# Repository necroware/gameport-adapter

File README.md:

# Necroware's GamePort Adapter

Many people from the retro community still have their beloved joysticks and
gamepads from the early days. These devices often live their lives somewhere in
the dark corners of our basements and we don't dare to throw them away, because
of nostalgic reasons. They remind us so much of our childhoods, where we played
our Wing Commanders, X-Wings, Descents and many other games. These old joysticks
were all made to be connected to the game port, usually on a sound card. But
by the end of 90's and beginning of 2000's game ports vanished from our
computers and were replaced by USB and our old joysticks disappeared into the
past. Today not everybody has a full retro PC and many people are using their
modern computer with  DOSBox to play the old games, sometimes with a modern
USB joystick. But wouldn't it be great to play the old games with the same
joystick which we used back then? And this is where this adapter comes into
play. It can be used to connect gameport joysticks to a USB port.

GamePort Adapter Videos:
* [Part 1: Introduction](https://youtu.be/tSJLgCD8jeM)
* [Part 2: Updates](https://youtu.be/947DewHwbsE)

## How does it work?

The adapter is built around Arduino Pro Micro, which uses the same ATmega32U4
microcontroller as Leonardo. This microcontroller has built-in USB HID
capabilities and can be used to build HID input devices, like joysticks. The
adapter itself is super simple, the main brainwork was invested into the
software. Very much simplified, it reads the joystick states and sends the data,
via USB, to the computer, which thinks that it is communicating with a USB 
joystick.

## What is special about this one?

There are already plenty of gameport to USB adapters for basic analog joysticks
and, as far as I know, there were some efforts to communicate with Sidewinder
joysticks by Microsoft as well. But there is no universal adapter, which would
work with different types of joysticks. This adapter implements multiple drivers
for various analog and digital joysticks, with an option to add more, in the 
future.

Features overview:
* Support for generic analog joysticks with 2/4 buttons and 2/4 axes
* Four switches to select joystick type
* Autodetection for various digital protocol joysticks
* Auto-Calibration
* Very low input lag

## What is the difference between analog and digital joystick?

Many people call button-only joysticks or gamepads digital. This is kind of
right, because a button is either pressed or not. You can't have an analog
values in between. However by digital, in this case, we mean something different.
A gameport contains 15 pins, 8 of which are used for joystick communication. 4
pins are for buttons and carry digital values in sense of on/off and 4 pins are
for analog axes, which deliver voltage somewhere between 0V and 5V. Joysticks
which were made in the early days used this pinout. They could have a
maximum of 4 buttons and 4 axes and were DOS compatible. Later, in the time of
Windows 95/98 many joysticks were made to be plugged into a gameport as well,
but they were not limited to 4 buttons and 4 axes. They had a lot more exciting
features, like hat switches and throttle controls. But how did this work? Well
the manufacturers implemented their drivers to communicate with the joystick via
gameport using a proprietary communication protocol. For example, by using one
pin of the gameport as clock and another one as data, the possibilities were
almost limitless. Such joysticks are called digital as well, because they used
digital protocols to communicate with the PC. And suddenly, many features were
possible, but the price of these features was the lost compatibility to DOS. You
couldn't just plug such a joystick into the gameport and expect it to work in
old DOS games. The plug was the same, but the signaling was completely different.

## Which joysticks does this adapter support?

Currently, the following drivers are implemented. To select the right driver, you
have to use four switches, as shown in the table. The switches may be changed or
extended in the future, so please pay attention to the updates.

Joystick Model               | Buttons | Axes  |  Hat | SW1-4 | Protocol   | Comments
-----------------------------|---------|-------|------|-------|------------|------------------------------------
Generic Analog               | 2       | 2     | 0    | 0000  | Analogue   |
Generic Analog               | 4       | 2     | 0    | 1000  | Analogue   |
Generic Analog               | 4       | 3     | 0    | 0100  | Analogue   | 3rd Axis is throttle
Generic Analog               | 4       | 4     | 0    | 1100  | Analogue   |
CH FlightStick               | 4       | 4     | 1    | 0010  | Analogue   |
CH F16 Combat Stick          | 10      | 3     | 1    | 0110  | Analogue   |
ThrustMaster                 | 4       | 3     | 1    | 1010  | Analogue   | FCS MARK I/II & PFCS
ThrustMaster Millenium 3D    | 6       | 4     | 1    | 0101  | TMDC       | 
Sidewinder GamePad           | 10      | 2     | 0    | 1110  | Sidewinder |
Sidewinder 3D Pro            | 8       | 4     | 1    | 1110  | Sidewinder |
Sidewinder 3D Pro Plus       | 9       | 4     | 1    | 1110  | Sidewinder | First version of Precision Pro
Sidewinder Precision Pro     | 16      | 4     | 1    | 1110  | Sidewinder | Shift doubbles the buttons
Sidewinder FFB Pro           | 16      | 4     | 1    | 1110  | Sidewinder | FFB not yet implemented
Sidewinder FFB Wheel         | 8       | 3     | 0    | 1110  | Sidewinder | FFB not yet implemented
Sidewinder Freestyle Pro     | 10      | 3     | 1    | 1110  | Sidewinder | 3rd axis is throttle
Gravis GamePad Pro           | 10      | 2     | 0    | 0001  | GrIP       |
Logitech WingMan Extreme     | 6       | 3     | 1    | 1001  | ADI        |
Logitech CyberMan 2          | 8       | 6     | 0    | 1001  | ADI        |
Logitech WingMan Interceptor | 9       | 3     | 3    | 1001  | ADI        | 2 hats are mapped as 4 axes
Logitech ThunderPad Digital  | 8       | 2     | 0    | 1001  | ADI        | Directional buttons mapped as 2 axes
Logitech WingMan Gamepad     | 11      | 2     | 0    | 1001  | ADI        | Directional buttons mapped as 2 axes
Logitech WingMan Light       | 2       | 2     | 0    | 0000  | Analogue   |

*Remarks:*

- Please pay attention to how the same switches are used for different families
of digital devices. This is possible due to fully digital communication. Using
this method, the adapter implements autodetection as soon as it knows, that it
is connected to a digital joystick.
- Currently, only the drivers for the listed Sidewinder devices are implemented,
since I have no other models at hand. The Precision Pro works natively on USB
as well, but was still implemented, because we can.
- Gravis used their GrIP protocol, which is currently implemented only for the
Gravis GamePad Pro, but without daisy chaining possibility so far.
- The implementation of the ADI protocol used by Logitech should work with all
the devices which support that protocol. However only the listed Logitech devices 
were tested so far.
- Likewise, for TMDC devices (ThrustMaster Direct Connect) only the Millenium 3D
has been tested. Rage 3D, Attack Throttle, Frag Master and Fusion Gamepad devices
are defined in code but button and axis mappings need verification.  

## Which joysticks were tested?

Many joysticks in the wild are using the same digital protocol or are backwards
compatible to the analog joysticks as they were used back in the days in DOS.
Following list contains all the devices which were reported by others as working
so far:

* CH Mach I+ (analog, 2-axes, 2-buttons)
* Gravis Analog Pro (analog)
* Gravis GamePad Pro
* Gravis PC GamePad (analog)
* InterAct UltraRacer PC (analog)
* Logitech CyberMan 2
* Logitech WingMan Extreme Digital
* Logitech WingMan Interceptor
* Logitech WingMan Light
* Logitech ThunderPad Digital
* Logitech WingMan Gamepad
* Medion Joypad MD9823 (analog, 4-axes, 4-buttons)
* QuickShot QS-123E "Warrior 5" (analog)
* Quickshot QS-146 "Intruder 5" (analog)
* Quickshot QS-151 "Aviator" (analog)
* QuickShot QS-201 "Super Warrior" (analog)
* QuickShot QS-203 "Avenger" (analog)
* Sidewinder 3D Pro
* Sidewinder 3D Pro Plus
* Sidewinder ForceFeedBack Pro
* Sidewinder ForceFeedBack Wheel
* Sidewinder Freestyle Pro
* Sidewinder GamePad
* Sidewinder Precision Pro
* ThrustMaster Millenium 3D Inceptor 

Sidewinder 3D Pro can be switched between analog and digital mode and in analog
mode it can emulate the ThrustMaster and CH FlightStick. That's why you see them in
the table above. Unfortunately I don't possess those joysticks in reality, so it may
be that the implementation is not quite correct.

## What is auto calibration?

Old analog joysticks have resistors inside, which are specified to be 100 kOhm.
Unfortunately, these resistors are either worn out, bad quality or were wrong from
the beginning. Therefore most of the generic analog joysticks had adjustment
screws to correct the center point of the joystick. Also many games had
calibration options in their settings to readjust the joystick. With USB and new
digital solutions the calibration was not required anymore and was completely
implemented in the joysticks and/or drivers. Many modern games have no option
to re-calibrate the joystick anymore. If we try to play such newer games with
an old analog joystick through this adapter, the joystick center point would be
totally offset. That's why the adapter implements auto calibration internally and
presents already corrected values to the operation system. 

__ATTENTION__: a hard requirement for using the analog joysticks is that during 
plugging into the USB port all axes must be in their middle state, because all
the subsequent calibration happens based on the initial state.

## Technical insights into implementation

The code is well documented, so if you are interested in the details, feel free
to take a look into the driver implementation. All the analog joysticks were
actually a straight forward task, but the Sidewinder digital protocol was kind 
of tough. There are already some implementations of Sidewinder protocol made for
Arduino. However, they are mostly only for the Sidewinder GamePad and not really 
universally made. In the end I was heavily inspired by the Linux Sidewinder 
driver implementation. The code you can see in this project is a complete rewrite, 
I just took the Linux driver implementation as a reference to understand how it 
works. Also the Sidewinder patent US#5628686A helped a lot, especially with 
switching between digital and analog mode for Sidewinder 3D Pro.

In opposition to the already mentioned Sidewinder for Arduino implementations,
this one doesn't rely on interrupts. This implementation is from a similar idea 
to what the Linux driver does. It polls the port and makes a lot of things
simpler due to synchronous process. The biggest problem was that the Sidwinder
devices send the data incredibly fast, with a clock pulse of only 5us. It was
not possible to use Arduino's digitalRead(...) function for that. It was too
slow with about 2.7us per call on an Arduino Pro Micro of 16MHz.  It simply
made it impossible to poll 5us pulses, with such a slow function, not even
considering doing something with the data in between. So out of that need, my 
own implementation came about, which is up to 50% faster and needs only about 
1.6us per call, on the same hardware. The custom I/O functions made it possible
to read the data with the speed which a Sidewinder joystick requires. The best 
part is that the code is written in pure C++. It is very simple to read and to 
use. There are no macros, no assembler or any dirty hacks, just a lot of
optimization.

## Bill of materials (BOM)

The hardware is super simple. To build an adapter you'll need the PCB from this
project and following parts:

Part    |  Qty  | [LCSC](https://lcsc.com/) #  | [Digikey](https://www.digikey.com/) #                | [Mouser Electronics](https://www.mouser.com/) # | Comment
--------|-------|---------|--------------------------|----------------------|------------------------------------------
CONN1   |   1   | C77835  | 609-5371-ND              | 523-L77SDA15SA4CH4F  | DB15 female connector
R1..R4  |   4   | C172965 | 13-MFR-25FTE52-100KCT-ND | 603-MFR-25FTE52-100K | 100 kOhm resistors
SW1     |   1   | C15781  | 2449-KG04ET-ND           | 642-DS04T            | DIP-4 switch
U1      |   1   | C72120  | ED3051-5-ND              | 649-DILB24P-223TLF   | DIP24 Socket (optional)
U1      |   1   |   N/A   | 1568-1060-ND             | 474-DEV-12640        | Arduino Pro Micro (ATmega32U4 16MHz, 5V), including two 12 pin header connectors, MicroUSB version (see "Known issues")

## Known issues

* *Some axes on an analog joystick are offset*

   Auto calibration requires all the axes to be in the center position during 
   initialization. Please see the paragraph about auto calibration.

* *Joystick doesn't work*

   Make sure that you are using one of supported joysticks or a joystick which can
   work in legacy analog mode

* *MicroUSB port on the Arduino is not stable enough*

   Use the USB-C version of the Arduino instead.  
   Or always keep the MicroUSB cable attached to the Arduino MicroUSB version to avoid further wear and apply plug/unplug operations only on the remote side of the cable.

## How to help the project?

The best way is to implement more drivers. Since I have only the joysticks
mentioned above, I can't contribute more than what is currently included.

## Special thanks

I would like to give some special thanks to *Creopard* from the German 
dosreloaded.de community for providing me the mentioned joysticks. Without that
donation this project wouldn't be possible. Especially dealing with Sidewinder
3D Pro was a very exciting task.

## Links
* [Linux Sidewinder Driver](https://github.com/torvalds/linux/blob/master/drivers/input/joystick/sidewinder.c)
* [Sidewinder patent](https://patents.google.com/patent/US5628686A/en)
* [Creopard Retro Site](https://www.creopard.de/)

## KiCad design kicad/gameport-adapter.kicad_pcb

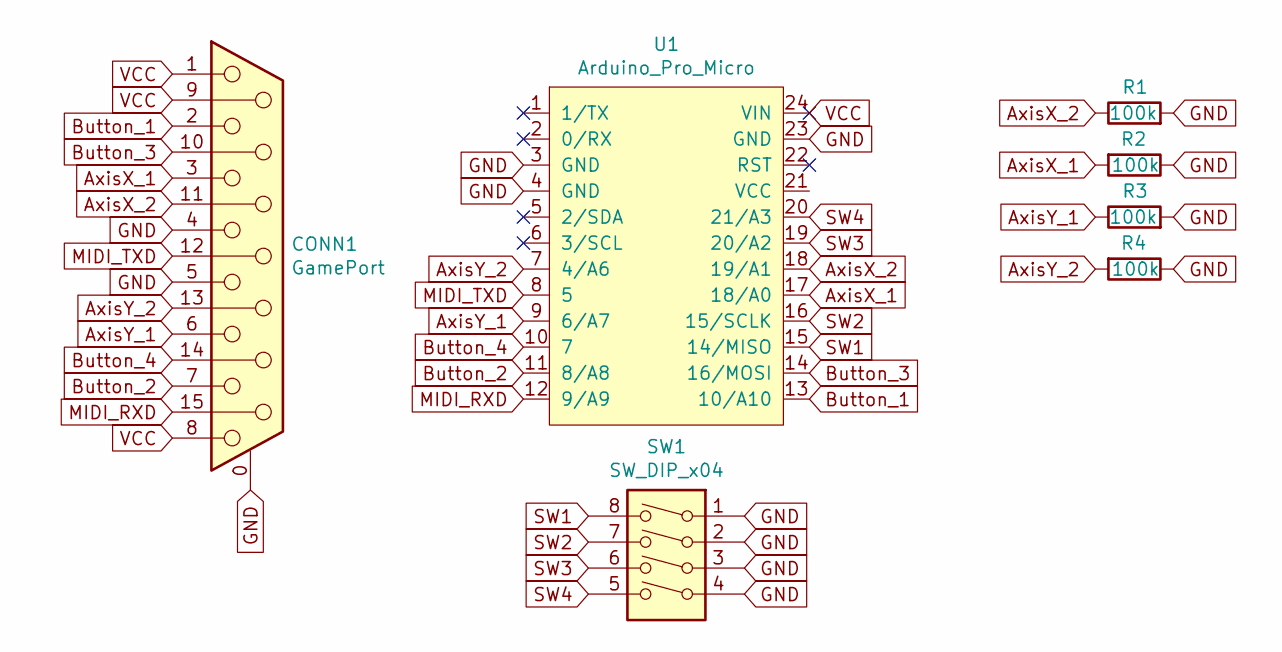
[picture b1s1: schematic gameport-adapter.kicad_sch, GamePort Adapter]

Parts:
CONN1: GamePort; DSUB-15_Female_Horizontal_P2.77x2.84mm_EdgePinOffset7.70mm_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; LCSC C77835
R1, R2, R3, R4: 100k; R_Axial_DIN0204_L3.6mm_D1.6mm_P7.62mm_Horizontal; LCSC C172965
SW1: SW_DIP_x04; SW_DIP_SPSTx04_Slide_9.78x12.34mm_W7.62mm_P2.54mm; LCSC C15781
U1: Arduino_Pro_Micro; DIP-24_W15.24mm_Socket; LCSC C72120

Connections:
AxisX_1: CONN1.3, R2.2, U1.17 (18/A0)
AxisX_2: CONN1.11 (P111), R1.1, U1.18 (19/A1)
AxisY_1: CONN1.6, R3.1, U1.9 (6/A7)
AxisY_2: CONN1.13, R4.2, U1.7 (4/A6)
Button_1: CONN1.2, U1.13 (10/A10)
Button_2: CONN1.7, U1.11 (8/A8)
Button_3: CONN1.10, U1.14 (16/MOSI)
Button_4: CONN1.14, U1.10 (7)
GND: CONN1.0 (PAD), CONN1.4, CONN1.5, R1.2, R2.1, R3.2, R4.1, SW1.1, SW1.2, SW1.3, SW1.4, U1.3 (GND), U1.4 (GND), U1.23 (GND)
MIDI_RXD: CONN1.15, U1.12 (9/A9)
MIDI_TXD: CONN1.12, U1.8 (5)
SW1: SW1.8, U1.15 (14/MISO)
SW2: SW1.7, U1.16 (15/SCLK)
SW3: SW1.6, U1.19 (20/A2)
SW4: SW1.5, U1.20 (21/A3)
VCC: CONN1.1, CONN1.8, CONN1.9, U1.24 (VIN)

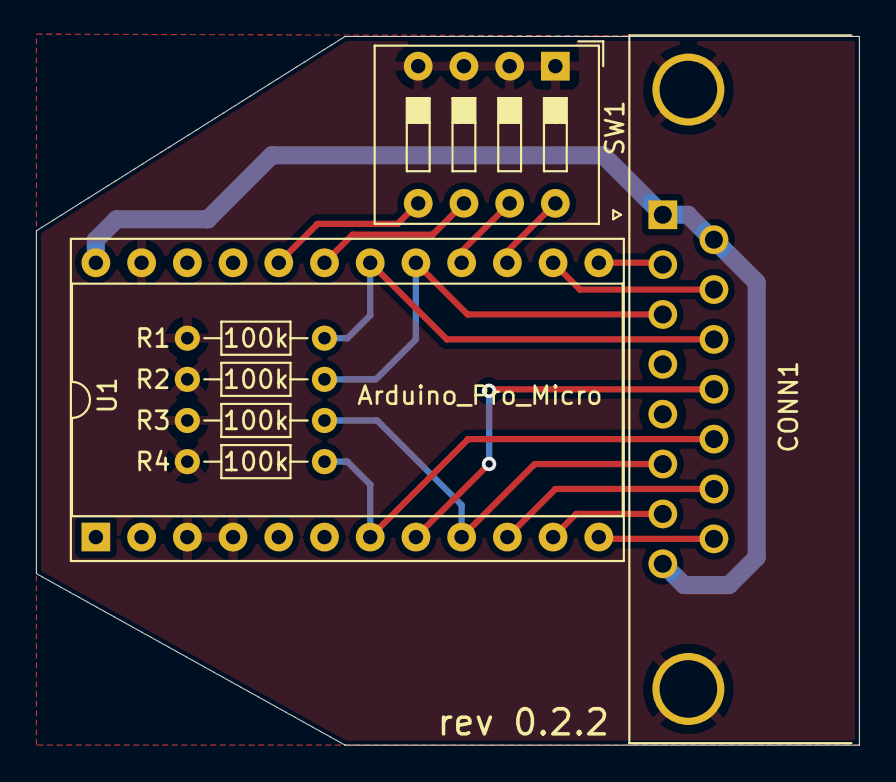
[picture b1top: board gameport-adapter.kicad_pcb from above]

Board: 2 copper layers, 45.7 x 39.4 mm, 7 parts (0 on the bottom side), 16 nets.

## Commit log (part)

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2020-11-23 Add gerber files, minor cleanup
2020-11-23 Update LSCS part number
2020-11-28 Set proper LCSC part number for the gameport
2020-11-28 Updated PCB
2021-01-07 Add necroware library
2021-01-07 Switched to Arduino Pro Micro
2021-03-12 Add pull-down resistors to analog pins
2021-04-01 OSHW logo, silk layer fixes
2021-04-20 Move socket towards connector
2021-04-27 Add initial code for generic joysticks
2021-04-27 Rotated switch order
2021-04-28 Add Sidewinder GP Pro support
2021-04-28 Add initial support for ThrustMaster
2021-04-28 Code cleanup
2021-05-04 Massive refacturing.
    - Extracted AnalogJoystick parts
    - Improved DigitalPin
    - Renamed Joystick -> Driver
    and more...
2021-05-04 Code cleanup in HID descriptors
2021-05-04 Add AnalogJoystick implementation
2021-05-11 Separated Sidewinder basics
2021-05-14 Implemented common base for sidwinder joysticks
2021-05-14 Implemented Sidewinder driver (working)
2021-05-14 Set Hat Switch range to 1-8
2021-05-15 Renamed all drivers to HidClass
2021-05-15 Add GPLv3 license text
2021-05-15 Deactivate Serial
2021-05-15 Add a lot of comments in the code
2021-05-15 Deactivated Serial
2021-05-15 Minor refactoring
2021-05-15 Readme
2021-05-16 Add image, add BOM, known issues etc...
2021-05-16 Fixed HID descriptions to improve Windows XP compatibility
2021-05-17 Add JoystickB4A3 driver, switches reordered
2021-05-26 Reduced cooldown for Sidewinder to reduce latency
2021-05-26 Code cleanup, use log functions
2021-05-26 Workaround SW 3D Pro reset problem
2021-05-30 Fix USB z-axis IDs
2021-05-30 Try harder to enable digital mode on sidewinder 3d pro
2021-05-31 Add Sidewinder Precision Pro support
2021-05-31 Minor code cleanup
2021-05-31 Increased input buffer again.
    The size of input buffer should be higher, than the biggest possible
    input length. In case the joystick transmits more bits, than expected,
    it can be used for error detection.
2021-06-01 Comment typo fix
2021-06-01 Remove fixed issue from readme
2021-06-01 Add clang-format
2021-06-01 Code format, switch case allignment
2021-06-02 Increased precision for Sidewinder joysticks.
    Now using full 10-bit range for the axes instead of 8-bit as before.
2021-06-02 Change some code format rules
2021-06-16 Rev.3 with miniusb and reset button
2021-06-19 Set pin mode on DIP switch pins for Sparkfun Pro Micro compatibility
2021-07-16 Updated the list of tested joysticks
2021-08-04 Updated wide pro micro footprint
2021-08-23 Add Digikey part numbers
2021-08-23 Update formatting
2021-09-14 Move InterruptStopper into own header
2021-10-10 initial implementation
2021-10-18 Code sends information
2021-10-20 Reimplement Packet.print() and remove some logs.
2021-10-20 Update Description for sidewinder FFB wheel
2021-10-22 Fix code following review
2021-10-22 Remove documents from the project.
    The origin of the documents is unclear and due to possible license
    issues, we should keep all documents outside. May be as links in the
    documentation.
2021-10-22 Fix timing issue reading packets
2021-10-22 Add Sidewinder Wheel to the list of supported devices
2021-10-30 Massive USB code rewrite, analogue joysticks are working again
2021-10-31 Moved to single HID align in the end
2021-10-31 Reduced footprint of static data
2021-10-31 Code format, added missing GPL header
2021-10-31 Added missing utilities file
2021-10-31 Switched GrIP to the new USB implementation
2021-10-31 Fixed device ID position in the HID description
2021-11-01 First incomplete implementation of ADI/Logitech
2021-11-01 Fix device name to C string pointer
2021-11-01 First working logitech version
2021-11-01 Add secondary buttons
2021-11-01 Move logging into utilities
2021-11-01 Imroved code safety
2021-11-01 Add code documentation
2021-11-02 Code format
2021-11-02 Remove unused file
2021-11-03 Performance improvements
2021-11-04 Code refactoring
2021-11-04 Improved Sidewinder reset timings
2021-11-04 Switched to standard Buffer
2021-11-04 Increased cooldown again for SW GP
2021-11-05 Add 3bit/1bit mode support for the precision pro
2021-11-05 Add 3bit/1bit mode support for the FFB Wheel
2021-11-08 Fix buttons axes count for generic joystick
2021-11-15 Add delay between the updates for Logitech devices
2022-01-01 Add QuickShot QS-123E into tested devices
2022-01-17 Added Thrustmaster DirectConnect with Attack Throttle support.
2022-01-19 Add video on the GamePort Adapter in Readme.md
    The introduction video should be mentioned here :)
2022-01-19 Minor silk layer fixes, rev 0.2.1
2022-01-19 Update the readme
2022-01-27 Simplified the code
2022-01-29 Add update video to the list of videos
2022-01-29 Readme format
2022-02-07 DigitalPin wait() optimizations
2022-02-07 Reverted some unneeded changes
2022-02-08 Reduced bit read delay further
2022-03-04 Thrustmaster changes to address review feedback, tweak timing, and general structure changes
2022-03-04 Updated thrustmaster to be compatible with the latest digital input code
2022-03-05 Add files via upload
    Support for Saitek Cyborg 2000 and Saitek SP550
    Known issues:
    Require calibration for Saitek SP550 gamepad mode or after switching to Joystick mode
    Will show 6 buttons for Saitek Cyborg 2000 where it only have 4 buttons
2022-03-11 reset m_errors = 0; on init
    Without this if you have a package decode error after init it immediately calls init again instead of giving a bit of slack.
    E.g.
    init
    error
    error
    error
2022-03-19 Update gitignore to ignore gerber folder in kicad folder
    When generating the gerber files necessary for printing the PCB, the default output from Kicad is to put them into a subfolder of the folder containing the .pro folder, named gerber. Add a rule to th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
2022-03-20 Correct DIP Switch part at Mouser
2022-03-30 Revert back to original DIP24 Socket at LCSC
2022-03-30 Change Digikey/Mouser DIP part numbers to same style as LCSC
2022-03-30 Fix spacing
2022-06-10 Updated the "grocery list"
2022-06-20 Update GenericJoystick.h
    Replacing the fixed value with the actual "Axes" saves 56 byte in compiled sketch.
2022-06-20 Update GamePort.h
    Added descriptive information which GamePort pin is connected to the Arduino pin
2022-06-20 Fix currently unused GamePort<12> pin designation
    GamePort<12>should be pin 5 instead of pin 20, as pin 20 is already occupied by the DIP switch
2022-06-20 Add static assertion to the amount of axes
2022-06-21 Improve switch detection.
    Reading digital inputs in setup seems not always to work reliably, so
    the initialization moved into the loop and is triggered on the first
    iteration.
2022-06-21 Update the list of tested devices
2022-06-22 replace function delay() with delayMicroseconds()
    Replacing the only occurence of delay(5) with delayMicroseconds(5000) saves 72 bytes.
    In the corresponding asm file at address 0000031a this replaces the function
    <delay>with a shorter <delay.constprop.22> instruction.
2022-06-23 enable debug feature (Utilities.h)
    include DEBUG_LOG(...) definition here as it get included in all necessary files
2022-06-23 enable debug feature (Logitech.h)
    DEBUG_LOG( ) is getting replaced to log( ) during compilation, when __DEBUG__ is defined
2022-06-23 enable debug feature (HidJoystick.h)
    DEBUG_LOG( ) is getting replaced to log( ) during compilation, when __DEBUG__ is defined
2022-06-23 enable debug feature (Sidewinder.h)
    DEBUG_LOG( ) is getting replaced to log( ) during compilation, when __DEBUG__ is defined
2022-06-24 Update gameport-adapter.ino
    added DEBUG information
2022-06-24 Remove unused print( ) function in Buffer.h
2022-06-25 Upgrade project to KiCad 6.x
2022-06-27 Update Utilities.h
    switch to NDEBUG
2022-06-27 Update gameport-adapter.ino
    switch to NDEBUG
2022-06-29 move NDEBUG to Utilities.h and add InitLogging()
2022-06-29 Moved log macros to Utilities
2022-06-29 Added switchable debug feature, remove unused print( ) function (#33)
    * enable debug feature (gameport-adapter.ino)
    * enable debug feature (Utilities.h)
    include DEBUG_LOG(...) definition here as it get included in all necessary files
    * enable debug feature (Logitech.h)
    DEBUG_LOG( ) is getting replaced to log( ) during compilation, when __DEBUG__ is defined
    * enable debug feature (HidJoystick.h)
2022-06-29 Revert "Added switchable debug feature, remove unused print( ) function (#33)"
    This reverts commit 4b660cee41e534d15c8490c27ae6d526d54ff37d.
2022-07-03 Raise the maximum count of hats to 3
2022-09-13 Added driver for CH F16 Combat Stick
2022-09-14 Changes as requestes for pull request
2022-09-14 Hardened CH F16 code for buttons decoding
2022-09-15 Fixed typos in the documentation
2022-09-25 Refilled ground zones
2022-11-21 NE558 emulation
    NE558 legacy gameport emulation for https://github.com/mamut-tme/QuickJoy-M-5-SV-201
2023-01-21 SW FFB Pro: initial support
2023-01-24 unsuccessful attempt at reading ID
2023-02-01 Added Sidewinder ID read function, made some refactoring
2023-02-01 Refactoring and switch to universal readID function
2023-02-02 Added SW FFB Pro to the readme
2023-03-12 Trying to improve timing for the SW FFB Pro
2023-03-26 Fixed timings for FFB Pro
2023-03-26 Increase cooldown to 3ms
    This reduces the speed of subsequent packet reads and helps with the
    model detection. Otherwise FFB Pro is sometimes detected as GamePad.
2023-07-21 Add small delay to the initialization.
    Some arduinos seem not to get the input pins in time before the switch
    for the device type is been read. This can lead to incorrect joystick
    type report. Adding a delay between input pin setup and actual read
    should improve that behavior.
2023-09-18 Fix timeout for Logitech Wingman Interceptor
2023-09-18 Register secondary hats as axes
2023-09-20 Increased pulse duration to enable digital mode in Logitech
2023-10-12 Change the powersupply of the gameport to VIN/RAW rather than VCC
    In my case with the Sidewinder 3D Pro the joystick did not seem
    to run stable. Maybe there was too much power drawn from VCC?
2023-10-14 Pad USB HID descriptor after every block.
    This is a try to fix Windows 10/11 compatibility issues by adding
    padding to each block separately instead of one padding in the end.
2023-10-14 Add padding to get Sidewinder 3D Pro Hat working in windows
2023-10-14 Make padding dynamic depending on the number of "hat directions"
2023-10-19 Fix typos
    Fix a number of small typos detected by codespell.
2023-10-19 Refer to the GrIP Linux driver in the GrIP code
2023-12-28 Fixed typo in the function name
2024-01-07 Added Logitech WingMan Light to the table
2024-01-22 Updates to ThrustmasterAttackThrottle hat assignment This is based on changes to the way hats are handled in Joystick.h
2024-01-22 Added support for daisy-chained sidewinder gamepads
2024-01-25 Signifcantly reduced memory usage. Was using too much memory with 4 hid descriptors. Cut that back to 1. Fixed logic with joystick count where it was left uninitialized. Bumped joystick and sidewinde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
2024-02-17 Fixed USB descriptor generator
2024-02-18 Update list of tested joysticks
2024-02-18 Fix USB HID descriptor for Windows
2024-04-03 Added handling of USB endpoint limits for daisychained joysticks
2024-04-13 Update Sidewinder.h
    Throttle axis corrected (was inverted). Added codeswitch to allow using the shift button as originally intended. (off by default)
2024-04-14 Also applied the changes to SW FF Pro
    I remembered they have the same buttons, but I don't have an FF Pro anymore to test.
2024-05-05 Update list of tested devices
2024-11-18 Moved the required initialization delay from setup() to Logitech::enableDigitalMode()
    Simplified the ThunderPad Digitial detection code
    Optimized the directional buttons to axes remapping code
    Added the Logitech ThunderPad Digitial to the list of supported devices
2024-11-18 Corrected a typo in README.md
2024-11-18 Add support for Logitech ThunderPad Digital (#94)
    Add support for Logitech ThunderPad Digital
2024-12-03 Add support for Logitech WingMan Gamepad
2024-12-03 Add support for Logitech WingMan Gamepad (#95)
    Thank you for the contribution.
2025-06-06 Update README.md
    Add tested ThrustMaster models
2026-03-23 chore: add clang-format github action
